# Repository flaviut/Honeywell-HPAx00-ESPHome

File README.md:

# ESPHome replacement control board for Honeywell True HEPA Air Purifier.

[Demo of current firmware version](https://youtu.be/eWahNrPkl0M), HPA200_HEPA_Filter_V2.yaml

[Demo of older firmware version](docs/demo.mp4), hepa-filter.yaml
## Current Software Features
Currently the on device firmware recreates all of the factory features of the HPA200 with a few improvements. Connection to Home Assistant is not needed for any functions.
- Fan Speed
  - Pressing the power button will toggle thru the 4 fan speed and then off
  - Turbo button will go to highest fan speed immediately
- Timer
  - Pressing the "Clock" button will toggle thru 2, 4, 8hr run timers
- Filter buttons
  - Current filter life is now show constantly with the LEDs next to the respective buttons. Used life is indicated by color gradient green-yellow-red
  - Filter lifetime hours is configurable in firmware or via Home Assistant
  - Filter usage can be reset by long holding the respective "Check filter" button for 3 seconds
- Dimmer
  - Dimmer setting is now retained even when unplugged. Pressing the dimmer button will cycle between LED levels down to 0%. Pressing any UI button will change all LEDs to max brightness and then they will return to their dimmed values after 5 seconds.
- Home Assistant
  - The fan speed is exposed as a variable speed fan
  - The accumulated filter and prefilter hours are exposed as sensors
  - The filter lifetime values are exposed as Configuration numbers. This allows customization of these values via HA without changes to the firmware.

## Compatibility and Hardware Versions
Compatible with HPA200. It *is not* compatible with the HPA300 or HPA100. The repo title mentioning "HPAx00" is **incorrect**, only the HPA200 will work. The specific PCB design you see in this repo has only been tested in a V2 unit, but is expected to work in V1 units without issue.

I suggest checking compatibility by disassembling your unit and confirming the control panel looks similar and is 205mm between the two furthest apart touch button pads.

### HPA200 Internal PCB Versions
There are two known versions of the the HPA200 internal PCBs V1 and V2. The replacement control PCB is compatible with both of these versions however only the V1 units will need modifications to the power PCB mentioned below.

#### Version 1
EH-A-4200-C V1.00, designed 2012-10-12.

#### Version 2
EH-A-4200V2-C-V1.0, designed 2019-06-04

## BOM

### Desoldered from original

- 7x touchpad springs
- 1x cable assembly

### Hand-soldered on Control PCB

- 1x [D1 mini ESP32](https://github.com/r0oland/ESP32_mini_KiCad_Library) (Note: this is the 40 pin ESP32 D1 NOT the 20 pin ESP8266 D1 Mini, I used https://www.aliexpress.us/item/2251832671740023.html, "CH9102X drive")
- 1x 6.3V+, 100uF+, P=3.5mm through-hole capacitor (probably optional but needs to be installed on it's side on the top of the PCB or vertical on the bottom due to housing clearance)
- 4x 10-pin 2.54mm headers. 2x of these generally come with your D1 mini ESP32 kit, and you can likely repurpose the long female headers from the kit as the other 2x.

### SMD for Control PCB

- 5x 16V+, 1uF+, 0805 ceramic capacitor
- 10x SKC6812 LEDs
- 1x M7 SMA diode

### Power PCB

There V1 power PCB can not supply enough 5VDC for the ESP and new LEDs. Replacement of the 7805 linear voltage regulator with a modern switched power supply is required.
- 7805-compatible buck regulator module
  - First prototype used https://www.aliexpress.us/item/3256801422436146.html which is no longer listed
  - Currently listed equivalent https://www.aliexpress.us/item/3256807692095306.html
  - Or drop in 7805 replacement IC like this https://www.digikey.com/en/products/detail/xp-power/RBT05W24S05/26667098

The V2 Power PCB has a new 5V power supply that has enough power to support the new control board and no modifications are required.
#### Power PCB Version Images
V1 Power PCB

V2 Power PCB

## Installation

### PCB Ordering

To the right of this page is the releases area. This area contains all the
materials you need to order your PCB from your preferred board house. I used
JLCPCB, so that is likely easiest, especially if you'd prefer someone else to
do the SMD assembly.

Hand placed SMD and hotplate reflow is also possible. Here is a list of SMD parts from Digikey available as of 2025 Q4. Note these LEDs vary slightly from the ones in the JLC BOM and require a code change.
| Item | DK PN | Qty |
|----------|----------|----------|
| CAP CER 4.7UF 25V X5R 0805   | [1276-1244-1-ND](https://www.digikey.com/en/products/detail/samsung-electro-mechanics/CL21A475KAQNNNE/3886902)     | 5     |
| ADDRESS LED DISC SERIAL RGB 1=10    | [1528-1104-ND](https://www.digikey.com/en/products/detail/adafruit-industries-llc/1655/5154679)     | 10     |
| DIODE STANDARD 1000V 1A DO214AC    | [5399-M7CT-ND](https://www.digikey.com/en/products/detail/shenzhen-slkormicro-semicon-co-ltd/M7/21853078)     | 1     |
| CAP ALUM 100UF 20% 16V RADIAL TH | [UVP1C101MPD1TD](https://www.digikey.com/en/products/detail/nichicon/UVP1C101MPD1TD/4328297)     | 1     |

### Tools

1. T20 TORX bit, 2in long (V2 units require T20 pin in head security bit)
1. Philips #2 screwdriver
1. Spudger or flathead screwdriver
1. Soldering iron
1. Soldering wick
1. Solder

### Procedure

#### Disassembly

1. Unplug the unit from the wall. If you do not do this, there is a high risk of electric shock.
1. Remove the filter grill from the front of the device by pressing it inwards
1. 6 screw holes will be revealed on the sides of the unit, Unscrew these screws.
    * V1 - 2 of the screws were T20 screws, and the other 4 were #2 philips.
    * V2 - all screws are T20 pin in head security bit
1. The top of the unit still has four clips holding the front on. Use a spudger to release the top clips on the front side.
1. Remove the front panel of the unit.
1. 4 smaller philips screws will be revealed holding the top on. Unscrew these.
1. Use a spudger to release the top clips on the back side.
1. The top panel should easily come off.
1. Unscrew the screws holding the controls tray.
1. Unscrew the screws holding the control PCB.
1. Release the clips holding the control PCB in.
1. Unplug the control cable assembly from the power supply board.
1. Use the soldering iron and solder wick to remove the touchpad springs and the cable assembly.

#### Modifications

**Figure 1:**

1. Flash the D1 mini ESP32 with ESPHome via the USB port. See the config at [HPA200_HEPA_Filter_V2.yaml](HPA200_HEPA_Filter_V2.yaml) as a starting point.
1. Solder the touchpad springs on the top side of the replacement control board. This is the side of the control board with the LEDs.
1. Solder the cable assembly on the top side of the replacement control board.
1. Solder the D1 mini ESP32 on the reverse of the replacement control board, using the silk-screen outline as a guide.
1. **V1 Power supply boards only:** De-solder Q1 from the power-supply board. Replace it with a 7805-compatible buck regulator. The output pin is the one closest to the connector. (see Fig 1, a)
1. Re-install the power supply board. Note that the screw is flat-tipped and shorter than the others (Fig 1, b)
1. Insert the board into the control panel and reinstall all screws.

#### Re-assembly

**Figure 2:**

**Figure 3:**

Reverse steps to re-assemble. Some notes:

1. Make sure the motor wires are coming out of the hole indicated in Fig 2, a
1. First screw the electronics box to the lid (Fig 2, b)
1. Then screw the lid onto the rest of the unit (Fig 2, c)
1. When snapping the front of the device on, make sure the plastic next to the handle (Fig 3, a) is correctly snapped in on both sides

## Software

See the config at [hepa-filter.yaml](./hepa-filter.yaml) as a starting point. You will need to use ESP32 Touch Pad's `setup_mode` to calibrate touch thresholds for each unit variance between units can be large.

## Credits

- Thank you to [Keith Burzinski](https://github.com/kbx81) for reviewing my design through endless revisions!

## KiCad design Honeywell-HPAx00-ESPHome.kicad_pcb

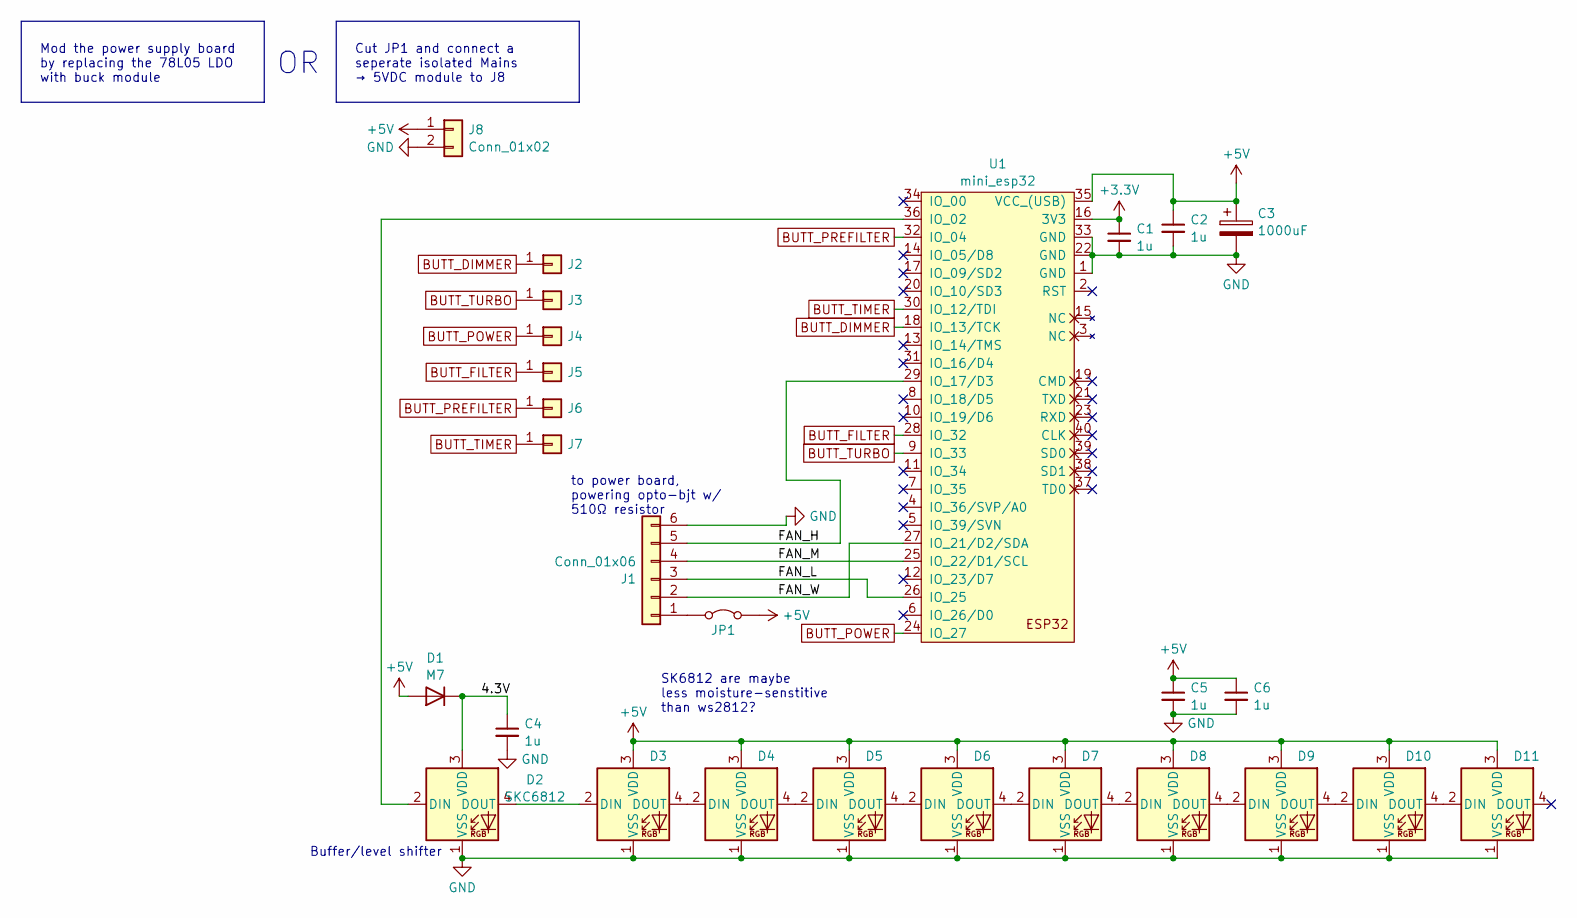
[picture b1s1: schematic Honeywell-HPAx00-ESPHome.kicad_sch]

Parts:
C1, C2, C4, C5, C6: 1u; C_0805_2012Metric_Pad1.18x1.45mm_HandSolder; LCSC C1779
C3: 1000uF; CP_Radial_D8.0mm_P3.50mm; LCSC C494544
D1: M7; D_SMA_Handsoldering; LCSC C95872
D2, D3, D4, D5, D6, D7, D8, D9, D10, D11: SKC6812; LED_SK6812_PLCC4_5.0x5.0mm_P3.2mm; LCSC C2890040
J1: Conn_01x06; JST_PH_S6B-PH-K_1x06_P2.00mm_Horizontal
J2, J3, J4, J5, J6, J7: Conn_01x01; Honeywell V1+2 Spring
J8: Conn_01x02; SolderWire-0.5sqmm_1x02_P4.6mm_D0.9mm_OD2.1mm_Relief
JP1: Jumper_2_Bridged; SolderJumper-2_P1.3mm_Bridged_RoundedPad1.0x1.5mm
U1: mini_esp32; ESP32_mini

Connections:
+3.3V: C1.1, U1.16 (3V3)
+5V: C2.1, C3.1, C5.1, C6.1, D1.2 (A), D3.3 (VDD), D4.3 (VDD), D5.3 (VDD), D6.3 (VDD), D7.3 (VDD), D8.3 (VDD), D9.3 (VDD), D10.3 (VDD), D11.3 (VDD), J8.1, JP1.2 (B), U1.35 (VCC_(USB))
/4.3V: C4.1, D1.1 (K), D2.3 (VDD)
/FAN_H: J1.5, U1.29 (IO_17/D3)
/FAN_L: J1.3, U1.26 (IO_25)
/FAN_M: J1.4, U1.25 (IO_22/D1/SCL)
/FAN_W: J1.2, U1.27 (IO_21/D2/SDA)
BUTT_DIMMER: J2.1, U1.18 (IO_13/TCK)
BUTT_FILTER: J5.1, U1.28 (IO_32)
BUTT_POWER: J4.1, U1.24 (IO_27)
BUTT_PREFILTER: J6.1, U1.32 (IO_04)
BUTT_TIMER: J7.1, U1.30 (IO_12/TDI)
BUTT_TURBO: J3.1, U1.9 (IO_33)
GND: C1.2, C2.2, C3.2, C4.2, C5.2, C6.2, D2.1 (VSS), D3.1 (VSS), D4.1 (VSS), D5.1 (VSS), D6.1 (VSS), D7.1 (VSS), D8.1 (VSS), D9.1 (VSS), D10.1 (VSS), D11.1 (VSS), J1.6, J8.2, U1.1 (GND), U1.22 (GND), U1.33 (GND)
unnamed: D2.2 (DIN), U1.36 (IO_02)
unnamed: D2.4 (DOUT), D3.2 (DIN)
unnamed: D3.4 (DOUT), D4.2 (DIN)
unnamed: D4.4 (DOUT), D5.2 (DIN)
unnamed: D5.4 (DOUT), D6.2 (DIN)
unnamed: D6.4 (DOUT), D7.2 (DIN)
unnamed: D7.4 (DOUT), D8.2 (DIN)
unnamed: D8.4 (DOUT), D9.2 (DIN)
unnamed: D9.4 (DOUT), D10.2 (DIN)
unnamed: D10.4 (DOUT), D11.2 (DIN)
unnamed: J1.1, JP1.1 (A)

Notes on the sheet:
Cut JP1 and connect a seperate isolated Mains → 5VDC module to J8
Buffer/level shifter
SK6812 are maybe less moisture-senstitive than ws2812?
to power board, powering opto-bjt w/ 510Ω resistor
Mod the power supply board by replacing the 78L05 LDO with buck module

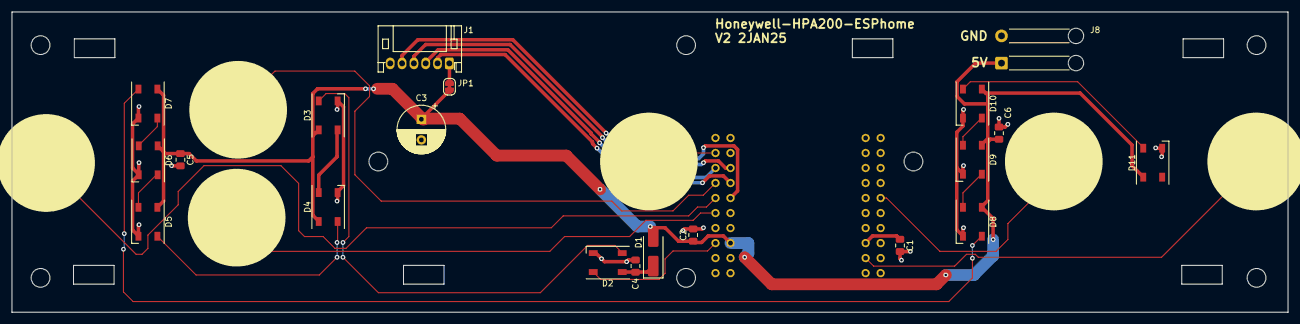
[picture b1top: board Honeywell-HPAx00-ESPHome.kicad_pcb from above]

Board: 2 copper layers, 215.9 x 50.8 mm, 27 parts (1 on the bottom side), 25 nets.

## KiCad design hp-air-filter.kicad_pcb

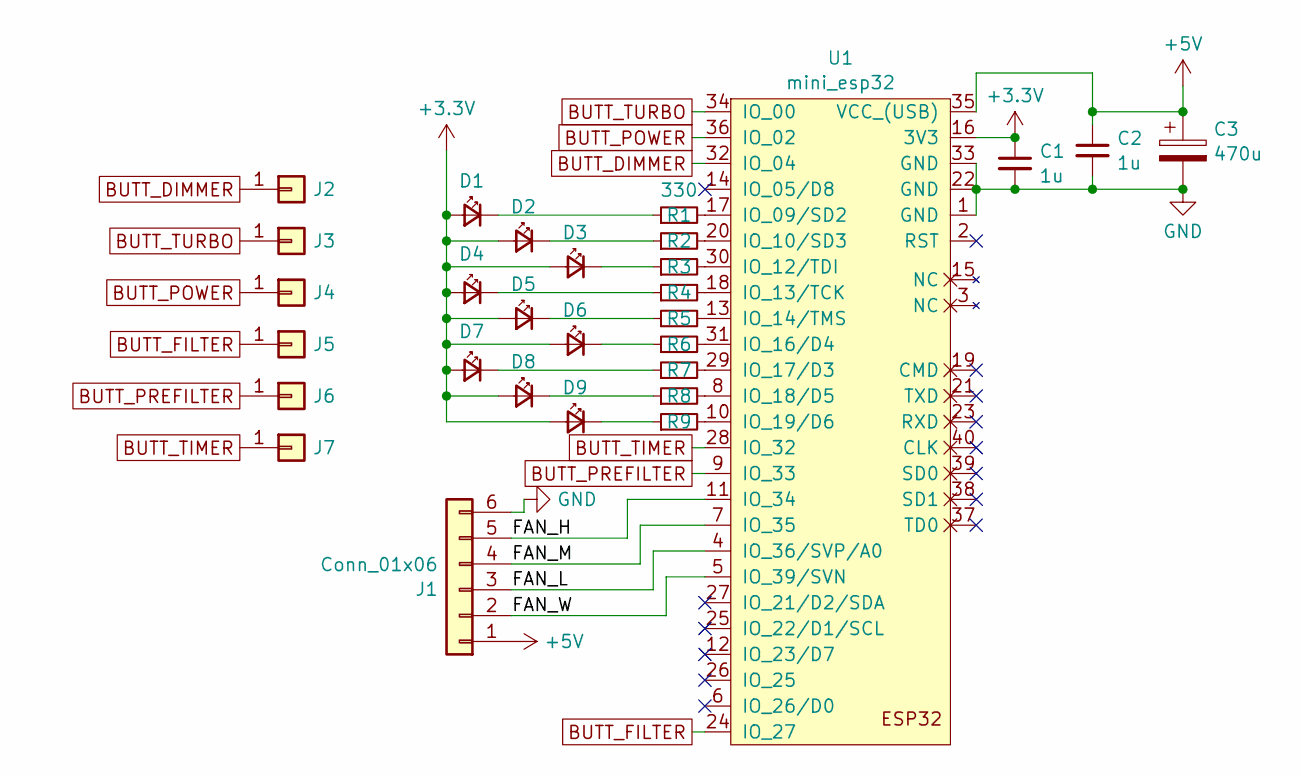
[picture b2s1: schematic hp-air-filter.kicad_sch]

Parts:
C1, C2: 1u; C_0805_2012Metric_Pad1.18x1.45mm_HandSolder; LCSC C1779
C3: 470u; CP_Radial_D8.0mm_P3.50mm; LCSC C6718380
D1, D2, D3, D4, D5, D6, D7, D8, D9: Red; LED_0603_1608Metric_Pad1.05x0.95mm_HandSolder; LCSC C2286
J1: Conn_01x06; JST_PH_S6B-PH-K_1x06_P2.00mm_Horizontal
J2, J3, J4, J5, J6, J7: Conn_01x01; TestPoint_THTPad_D1.5mm_Drill0.7mm
R1, R2, R3, R4, R5, R6, R7, R8, R9: 330; R_0603_1608Metric_Pad0.98x0.95mm_HandSolder; LCSC C23138
U1: mini_esp32; ESP32_mini

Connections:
+3.3V: C1.1, D1.2 (A), D2.2 (A), D3.2 (A), D4.2 (A), D5.2 (A), D6.2 (A), D7.2 (A), D8.2 (A), D9.2 (A), U1.16 (3V3)
+5V: C2.1, C3.1, J1.1, U1.35 (VCC_(USB))
/FAN_H: J1.5, U1.11 (IO_34)
/FAN_L: J1.3, U1.4 (IO_36/SVP/A0)
/FAN_M: J1.4, U1.7 (IO_35)
/FAN_W: J1.2, U1.5 (IO_39/SVN)
BUTT_DIMMER: J2.1, U1.32 (IO_04)
BUTT_FILTER: J5.1, U1.24 (IO_27)
BUTT_POWER: J4.1, U1.36 (IO_02)
BUTT_PREFILTER: J6.1, U1.9 (IO_33)
BUTT_TIMER: J7.1, U1.28 (IO_32)
BUTT_TURBO: J3.1, U1.34 (IO_00)
GND: C1.2, C2.2, C3.2, J1.6, U1.1 (GND), U1.22 (GND), U1.33 (GND)
unnamed: D1.1 (K), R1.1
unnamed: D2.1 (K), R2.1
unnamed: D3.1 (K), R3.1
unnamed: D4.1 (K), R4.1
unnamed: D5.1 (K), R5.1
unnamed: D6.1 (K), R6.1
unnamed: D7.1 (K), R7.1
unnamed: D8.1 (K), R8.1
unnamed: D9.1 (K), R9.1
unnamed: R1.2, U1.17 (IO_09/SD2)
unnamed: R2.2, U1.20 (IO_10/SD3)
unnamed: R3.2, U1.30 (IO_12/TDI)
unnamed: R4.2, U1.18 (IO_13/TCK)
unnamed: R5.2, U1.13 (IO_14/TMS)
unnamed: R6.2, U1.31 (IO_16/D4)
unnamed: R7.2, U1.29 (IO_17/D3)
unnamed: R8.2, U1.8 (IO_18/D5)
unnamed: R9.2, U1.10 (IO_19/D6)

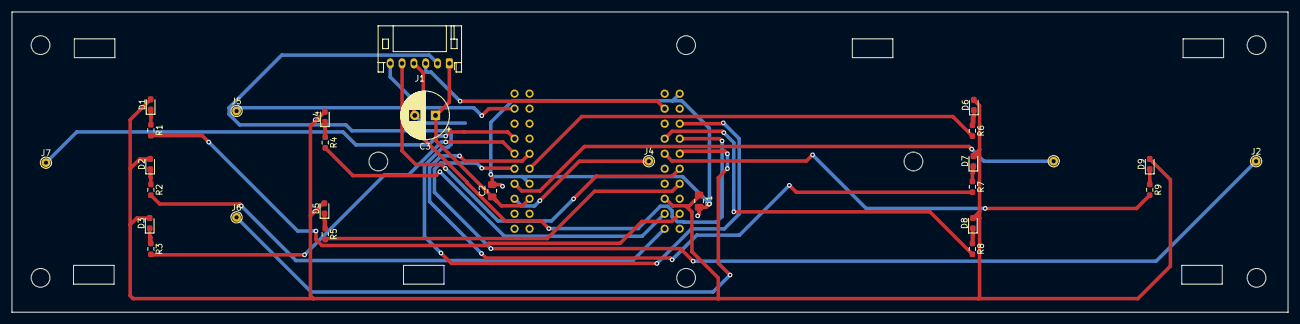
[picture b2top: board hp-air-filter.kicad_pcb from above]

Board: 2 copper layers, 215.9 x 50.8 mm, 29 parts (1 on the bottom side), 31 nets.

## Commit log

2024-01-30 Update based on feedback
2024-01-31 Update design
2024-02-04 final tweaks
2024-02-21 Fix issues from production
    1. clear space around buttons on ground plane
    2. increase capacitor to 4.7mF (1mF would be an absolute minimum)
    3. increase hole size for connector, since it's a very tight fit
2024-02-22 Update with complete instructions
2024-02-22 Update testing disclaimer
2024-02-22 Update software section
2024-02-22 Update demo
2024-02-22 Add PCB instructions
2024-02-22 Update demo video
2025-04-10 T20 bit
    Removed security, since T20 TORX security has an actual pin in the center. These are regular T20 TORX screws.
2025-04-11 Update README.md (#1)
2025-04-30 Add connector for extra 5V PSU
2025-04-30 Move prefilter to GPIO4 (#1)
2025-12-30 Major updates to readme, new device yaml, documentation of V2 hardware, light file organization.
2025-12-30 Fixed \ error for image links
2026-01-02 Updated PCB with new spring footprints
2026-01-05 Revise demo links in README.md
    Added YT link to current FW demo
